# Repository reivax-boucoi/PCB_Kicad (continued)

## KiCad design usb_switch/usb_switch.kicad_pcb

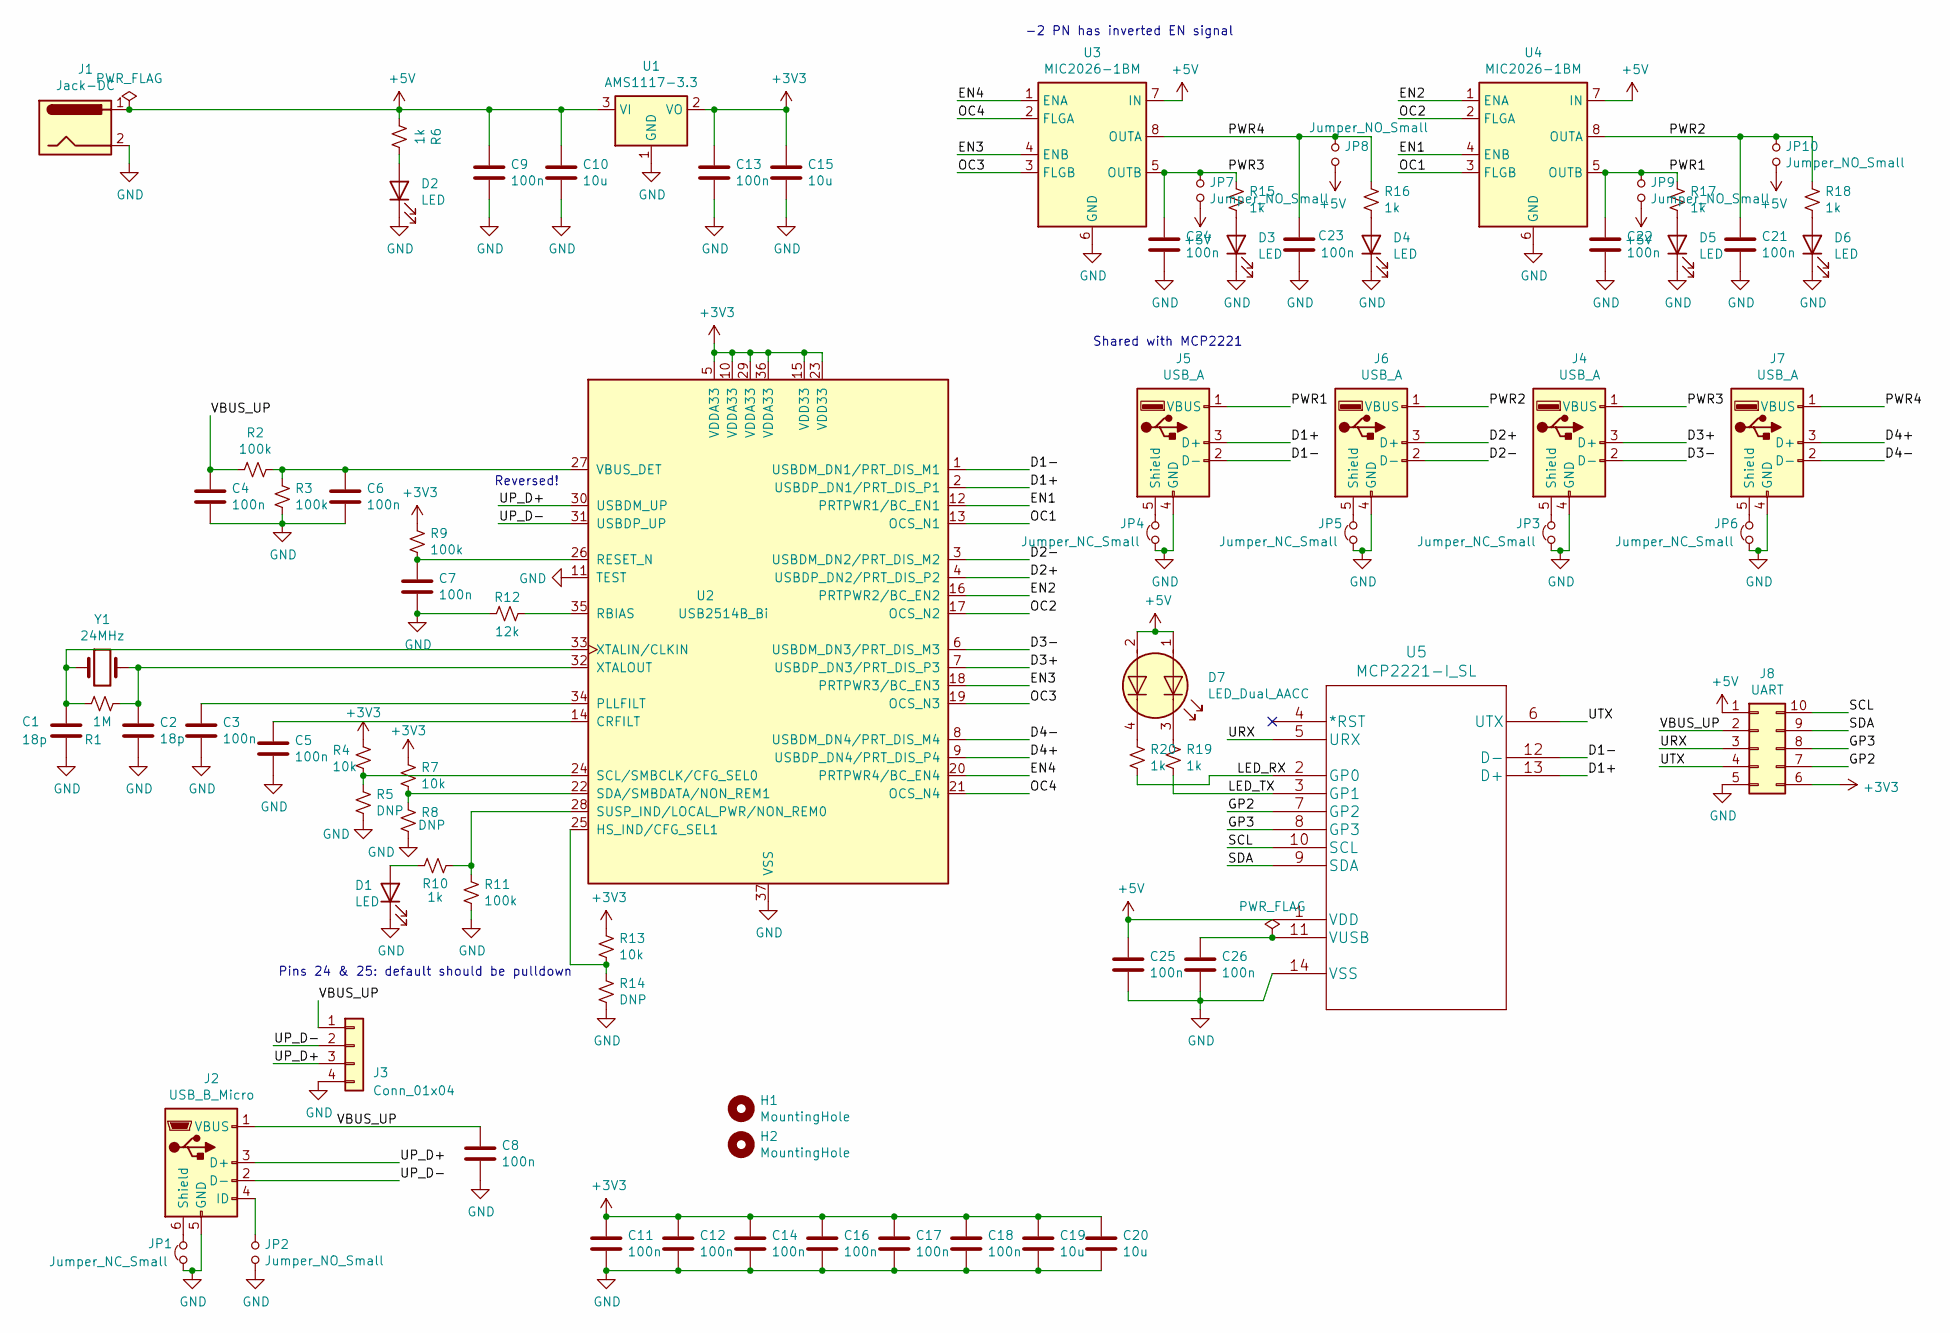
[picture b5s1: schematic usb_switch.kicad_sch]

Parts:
C1, C2: 18p; C_0603_1608Metric_Pad1.05x0.95mm_HandSolder
C3, C4, C5, C6, C7, C8, C9, C11, C12, C13, C14, C16, C17, C18, C21, C22, C23, C24, C25, C26: 100n; C_0603_1608Metric_Pad1.05x0.95mm_HandSolder
C10, C15, C19, C20: 10u; C_0603_1608Metric_Pad1.05x0.95mm_HandSolder
D1, D2, D3, D4, D5, D6: LED; LED_0603_1608Metric_Pad1.05x0.95mm_HandSolder
D7: LED_Dual_AACC; LED_SK6812_EC15_1.5x1.5mm
H1, H2: MountingHole; MountingHole_2.2mm_M2
J1: Jack-DC; BarrelJack_Wuerth_6941xx301002
J2: USB_B_Micro; USB_Micro-B_Molex_47346-0001
J3: Conn_01x04; PinSocket_1x04_P2.54mm_Vertical
J4, J5, J6, J7: USB_A; USB_A_Stewart_SS-52100-001_Horizontal
J8: UART; PinSocket_2x05_P2.54mm_Horizontal
JP1, JP3, JP4, JP5, JP6: Jumper_NC_Small; SolderJumper-2_P1.3mm_Bridged_RoundedPad1.0x1.5mm
JP2, JP7, JP8, JP9, JP10: Jumper_NO_Small; SolderJumper-2_P1.3mm_Open_RoundedPad1.0x1.5mm
R1: 1M; R_0603_1608Metric_Pad1.05x0.95mm_HandSolder
R2, R3, R9, R11: 100k; R_0603_1608Metric_Pad1.05x0.95mm_HandSolder
R4, R7, R13: 10k; R_0603_1608Metric_Pad1.05x0.95mm_HandSolder
R5, R8, R14: DNP; R_0603_1608Metric_Pad1.05x0.95mm_HandSolder
R6, R10, R15, R16, R17, R18, R20: 1k; R_0603_1608Metric_Pad1.05x0.95mm_HandSolder
R12: 12k; R_0603_1608Metric_Pad1.05x0.95mm_HandSolder
R19: 1k; R_0603_1608Metric
U1: AMS1117-3.3; SOT-223-3_TabPin2
U2: USB2514B_Bi; QFN-36-1EP_6x6mm_P0.5mm_EP3.7x3.7mm
U3, U4: MIC2026-1BM; SOIC-8_3.9x4.9mm_P1.27mm
U5: MCP2221-I_SL
Y1: 24MHz; Crystal_SMD_HC49-SD

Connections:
+3V3: C11.1, C12.1, C13.1, C14.1, C15.1, C16.1, C17.1, C18.1, C19.1, C20.1, J8.6, R4.1, R7.1, R9.1, R13.1, U1.2 (VO), U2.5 (VDDA33), U2.10 (VDDA33), U2.15 (VDD33), U2.23 (VDD33), U2.29 (VDDA33), U2.36 (VDDA33)
+5V: C9.1, C10.1, C25.1, D7.1 (A1), D7.2 (A2), J1.1, J8.1, JP7.2, JP8.2, JP9.2, JP10.2, R6.1, U1.3 (VI), U3.7 (IN), U4.7 (IN), U5.1 (VDD)
/D1+: J5.3 (D+), U2.2 (USBDP_DN1/PRT_DIS_P1), U5.13 (D+)
/D1-: J5.2 (D-), U2.1 (USBDM_DN1/PRT_DIS_M1), U5.12 (D-)
/D2+: J6.3 (D+), U2.4 (USBDP_DN2/PRT_DIS_P2)
/D2-: J6.2 (D-), U2.3 (USBDM_DN2/PRT_DIS_M2)
/D3+: J4.3 (D+), U2.7 (USBDP_DN3/PRT_DIS_P3)
/D3-: J4.2 (D-), U2.6 (USBDM_DN3/PRT_DIS_M3)
/D4+: J7.3 (D+), U2.9 (USBDP_DN4/PRT_DIS_P4)
/D4-: J7.2 (D-), U2.8 (USBDM_DN4/PRT_DIS_M4)
/EN1: U2.12 (PRTPWR1/BC_EN1), U4.4 (ENB)
/EN2: U2.16 (PRTPWR2/BC_EN2), U4.1 (ENA)
/EN3: U2.18 (PRTPWR3/BC_EN3), U3.4 (ENB)
/EN4: U2.20 (PRTPWR4/BC_EN4), U3.1 (ENA)
/GP2: J8.7, U5.7 (GP2)
/GP3: J8.8, U5.8 (GP3)
/LED_RX: R20.2, U5.2 (GP0)
/LED_TX: R19.2, U5.3 (GP1)
/OC1: U2.13 (OCS_N1), U4.3 (FLGB)
/OC2: U2.17 (OCS_N2), U4.2 (FLGA)
/OC3: U2.19 (OCS_N3), U3.3 (FLGB)
/OC4: U2.21 (OCS_N4), U3.2 (FLGA)
/PWR1: C22.1, J5.1 (VBUS), JP9.1, R17.1, U4.5 (OUTB)
/PWR2: C21.1, J6.1 (VBUS), JP10.1, R18.1, U4.8 (OUTA)
/PWR3: C24.1, J4.1 (VBUS), JP7.1, R15.1, U3.5 (OUTB)
/PWR4: C23.1, J7.1 (VBUS), JP8.1, R16.1, U3.8 (OUTA)
/SCL: J8.10, U5.10 (SCL)
/SDA: J8.9, U5.9 (SDA)
/UP_D+: J2.3 (D+), J3.3, U2.30 (USBDM_UP)
/UP_D-: J2.2 (D-), J3.2, U2.31 (USBDP_UP)
/URX: J8.3, U5.5 (URX)
/UTX: J8.4, U5.6 (UTX)
/VBUS_UP: C4.1, C8.1, J2.1 (VBUS), J3.1, J8.2, R2.2
GND: C1.2, C2.2, C3.2, C4.2, C5.2, C6.2, C7.2, C8.2, C9.2, C10.2, C11.2, C12.2, C13.2, C14.2, C15.2, C16.2, C17.2, C18.2, C19.2, C20.2, C21.2, C22.2, C23.2, C24.2, C25.2, C26.2, D1.1 (K), D2.1 (K), D3.1 (K), D4.1 (K), D5.1 (K), D6.1 (K), J1.2, J2.5 (GND), J3.4, J4.4 (GND), J5.4 (GND), J6.4 (GND), J7.4 (GND), J8.5, JP1.1, JP2.2, JP3.1, JP4.1, JP5.1, JP6.1, R3.2, R5.2, R8.2, R11.2, R12.2, R14.2, U1.1 (GND), U2.11 (TEST), U2.37 (VSS), U3.6 (GND), U4.6 (GND), U5.14 (VSS)
unnamed: C1.1, R1.1, U2.33 (XTALIN/CLKIN), Y1.1
unnamed: C2.1, R1.2, U2.32 (XTALOUT), Y1.2
unnamed: C3.1, U2.34 (PLLFILT)
unnamed: C5.1, U2.14 (CRFILT)
unnamed: C6.1, R2.1, R3.1, U2.27 (VBUS_DET)
unnamed: C7.1, R9.2, U2.26 (RESET_N)
unnamed: C26.1, U5.11 (VUSB)
unnamed: D1.2 (A), R10.1
unnamed: D2.2 (A), R6.2
unnamed: D3.2 (A), R15.2
unnamed: D4.2 (A), R16.2
unnamed: D5.2 (A), R17.2
unnamed: D6.2 (A), R18.2
unnamed: D7.3 (K1), R19.1
unnamed: D7.4 (K2), R20.1
unnamed: J2.4 (ID), JP2.1
unnamed: J2.6 (Shield), JP1.2
unnamed: J4.5 (Shield), JP3.2
unnamed: J5.5 (Shield), JP4.2
unnamed: J6.5 (Shield), JP5.2
unnamed: J7.5 (Shield), JP6.2
unnamed: R4.2, R5.1, U2.24 (SCL/SMBCLK/CFG_SEL0)
unnamed: R7.2, R8.1, U2.22 (SDA/SMBDATA/NON_REM1)
unnamed: R10.2, R11.1, U2.28 (SUSP_IND/LOCAL_PWR/NON_REM0)
unnamed: R12.1, U2.35 (RBIAS)
unnamed: R13.2, R14.1, U2.25 (HS_IND/CFG_SEL1)

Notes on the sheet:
Shared with MCP2221
Reversed!
Pins 24 & 25: default should be pulldown
-2 PN has inverted EN signal

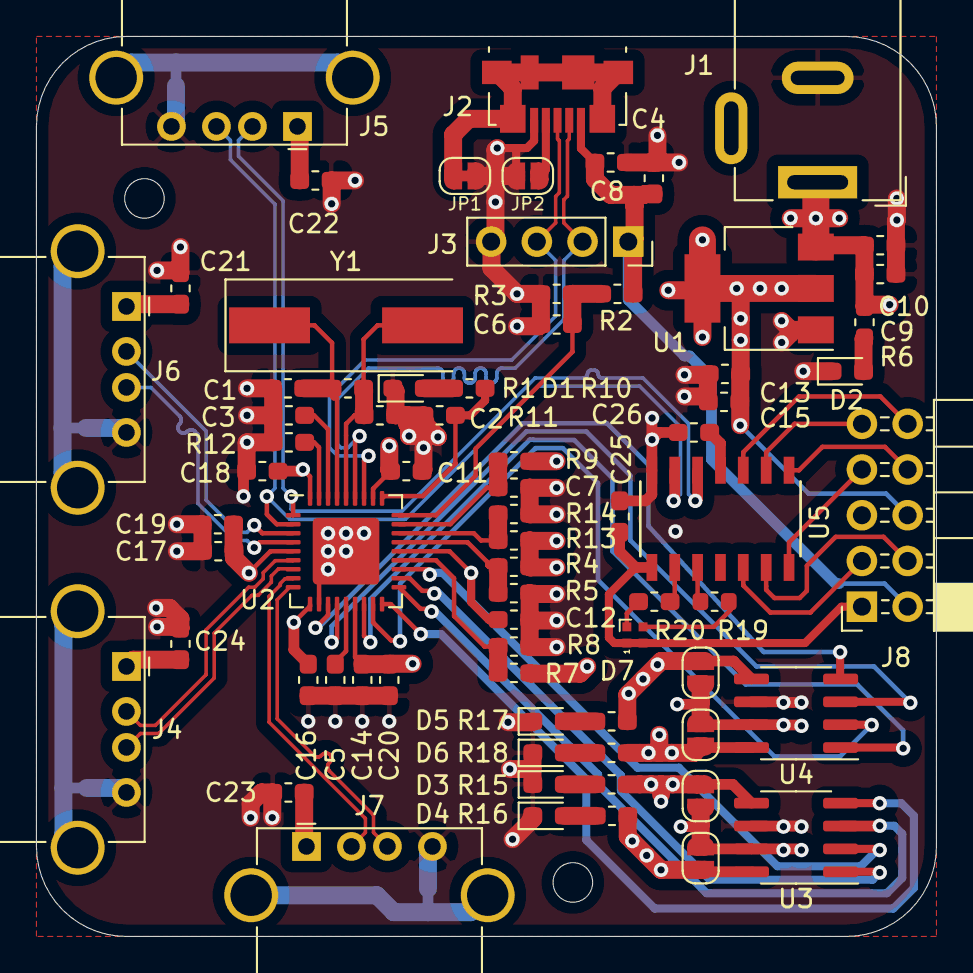
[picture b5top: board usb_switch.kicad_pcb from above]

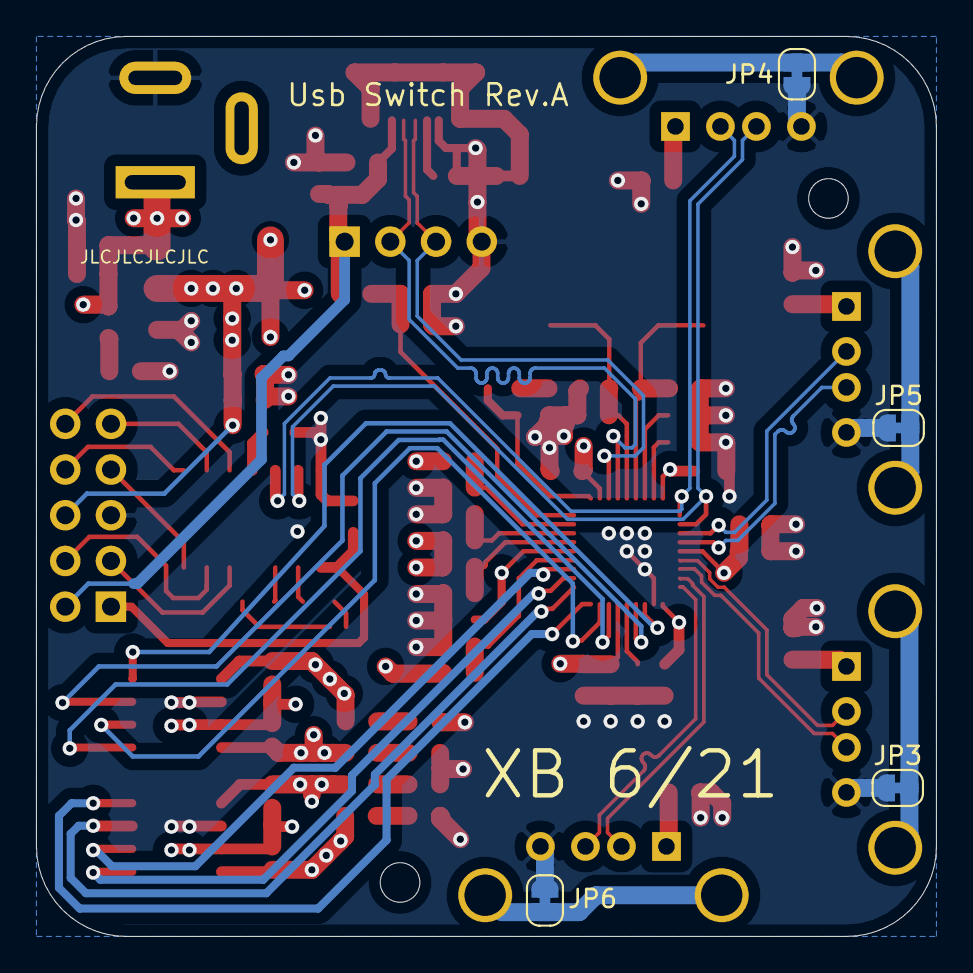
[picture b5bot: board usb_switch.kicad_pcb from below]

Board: 4 copper layers, 50.0 x 50.0 mm, 79 parts (4 on the bottom side), 60 nets.

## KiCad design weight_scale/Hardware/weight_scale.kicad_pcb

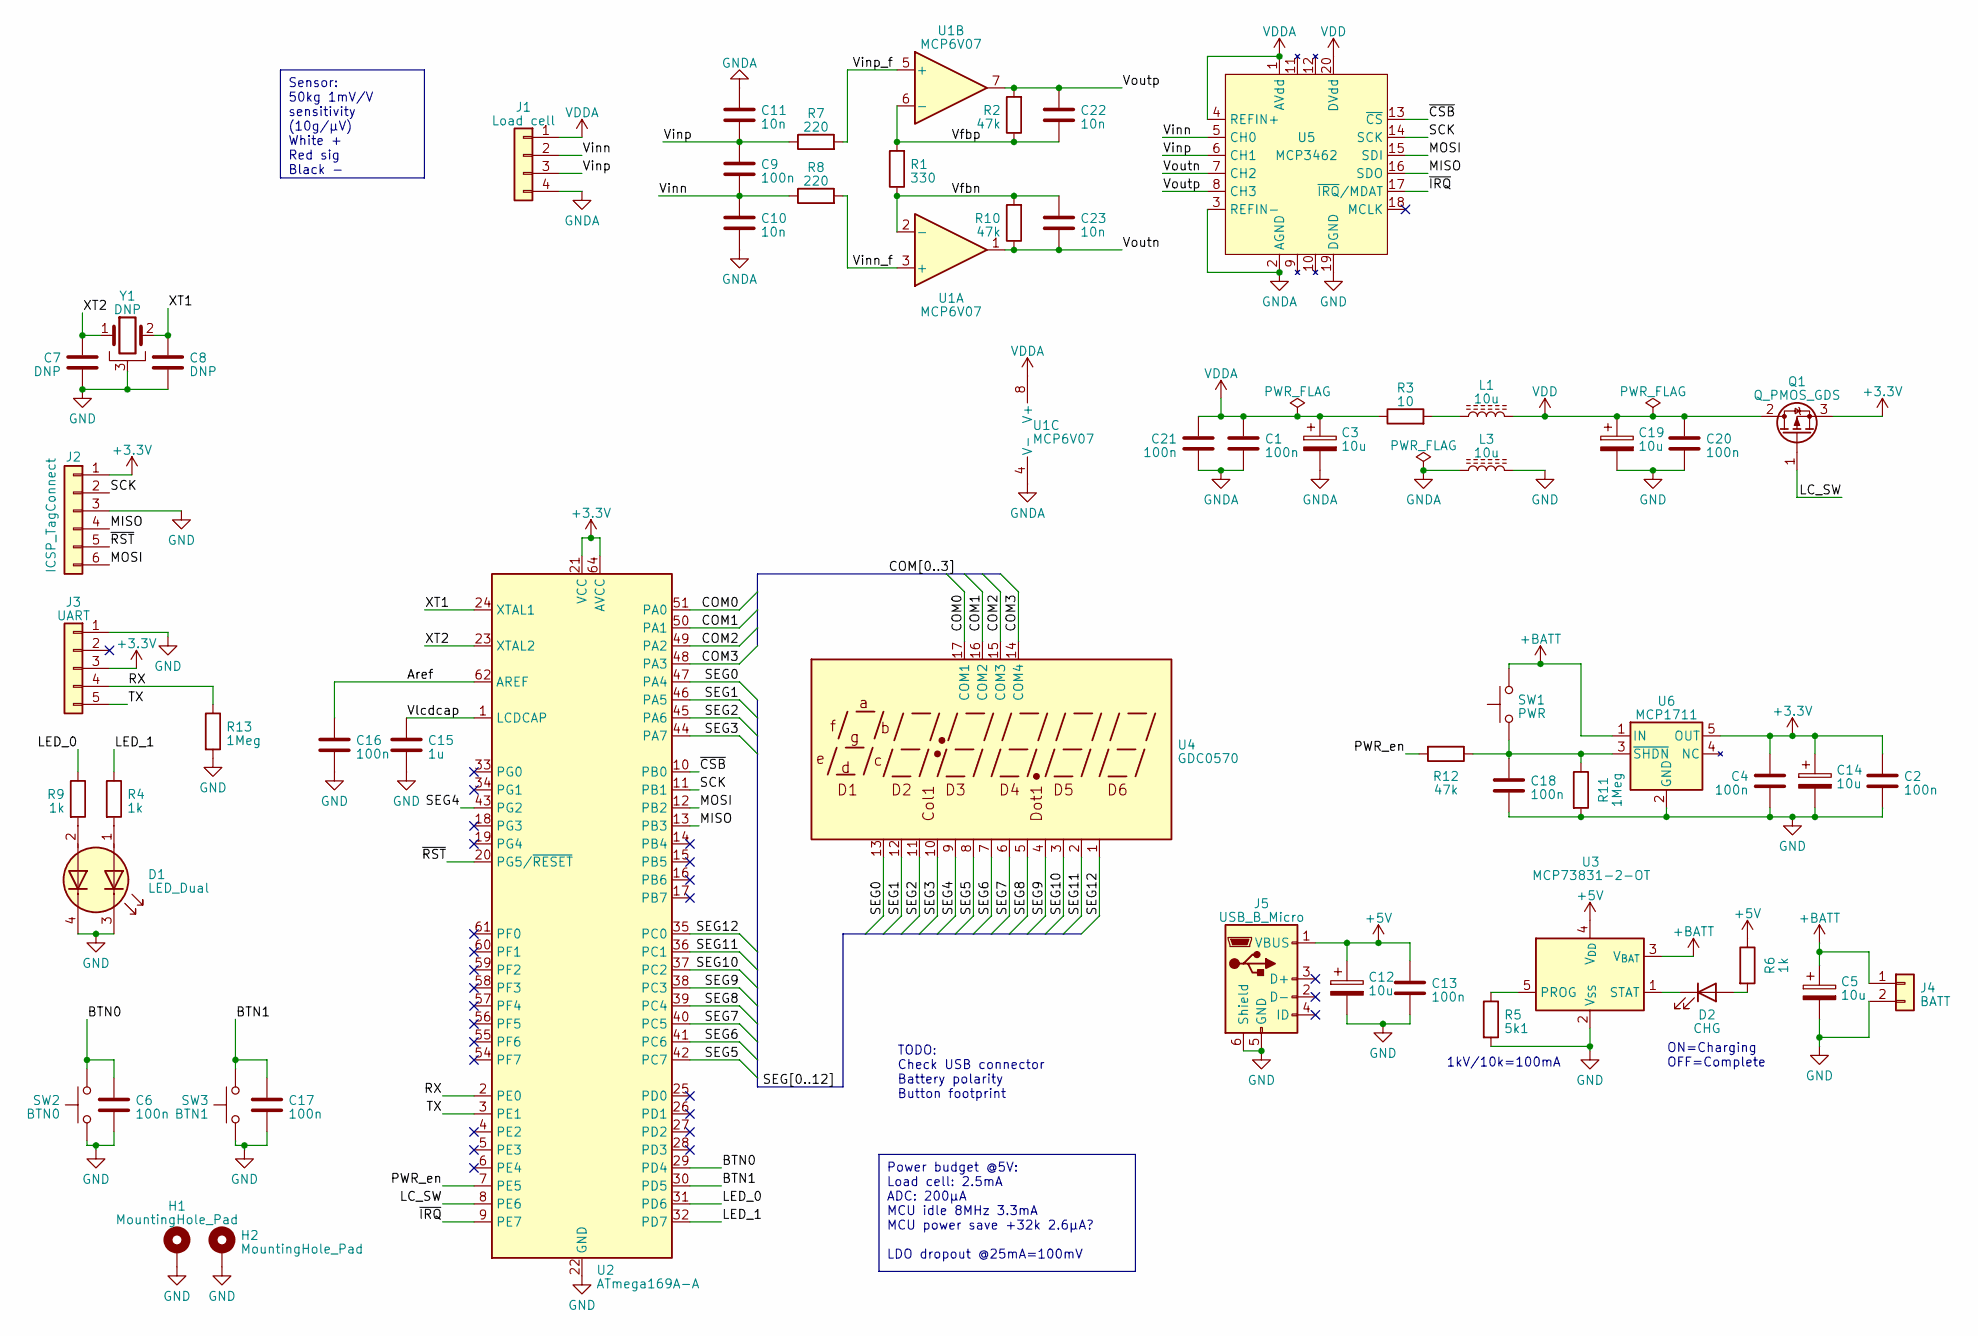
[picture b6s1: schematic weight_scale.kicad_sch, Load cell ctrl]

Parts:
C1, C2, C4, C6, C9, C13, C16, C17, C18, C20, C21: 100n; C_0805_2012Metric_Pad1.18x1.45mm_HandSolder
C3, C5, C12, C14, C19: 10u; C_1206_3216Metric_Pad1.33x1.80mm_HandSolder
C7, C8: DNP; C_0805_2012Metric_Pad1.18x1.45mm_HandSolder
C10, C11, C22, C23: 10n; C_0805_2012Metric_Pad1.18x1.45mm_HandSolder
C15: 1u; C_0805_2012Metric_Pad1.18x1.45mm_HandSolder
D1: LED_Dual; LED_Cree-PLCC4_3.2x2.8mm_CCW
D2: CHG; LED_0805_2012Metric_Pad1.15x1.40mm_HandSolder
H1, H2: MountingHole_Pad; MountingHole_3.2mm_M3_Pad_Via
J1: Load cell; 282834-4
J2: ICSP_TagConnect; Tag-Connect_TC2030-IDC-NL_2x03_P1.27mm_Vertical
J3: UART; PinSocket_1x05_P2.54mm_Vertical
J4: BATT; PinHeader_1x02_P2.54mm_Vertical
J5: USB_B_Micro; USB_Mini-B_Wuerth_65100516121_Horizontal
L1, L3: 10u; L_0805_2012Metric_Pad1.15x1.40mm_HandSolder
Q1: Q_PMOS_GDS; SOT-89-3_Handsoldering
R1: 330; R_0805_2012Metric_Pad1.20x1.40mm_HandSolder
R2, R10, R12: 47k; R_0805_2012Metric_Pad1.20x1.40mm_HandSolder
R3: 10; R_0805_2012Metric_Pad1.20x1.40mm_HandSolder
R4, R6, R9: 1k; R_0805_2012Metric_Pad1.20x1.40mm_HandSolder
R5: 5k1; R_0805_2012Metric_Pad1.20x1.40mm_HandSolder
R7, R8: 220; R_0805_2012Metric_Pad1.20x1.40mm_HandSolder
R11, R13: 1Meg; R_0805_2012Metric_Pad1.20x1.40mm_HandSolder
SW1: PWR; SW_PUSH_6mm_2pins
SW2: BTN0; SW_PUSH_6mm_2pins
SW3: BTN1; SW_PUSH_6mm_2pins
U1: MCP6V07; SOIC-8_3.9x4.9mm_P1.27mm
U2: ATmega169A-A; TQFP-64_14x14mm_P0.8mm
U3: MCP73831-2-OT; SOT-23-5
U4: GDC0570; GDC0570_LCD_6digits_2mmPitch
U5: MCP3462; TSSOP-20_4.4x6.5mm_P0.65mm
U6: MCP1711; SOT-23-5
Y1: DNP; Crystal_C26-LF_D2.1mm_L6.5mm_Horizontal_1EP_style2

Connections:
+3.3V: C2.1, C4.1, C14.1, J2.1, J3.3, Q1.3 (S), U2.21 (VCC), U2.52 (VCC), U2.64 (AVCC), U6.5 (OUT)
+5V: C12.1, C13.1, J5.1 (VBUS), R6.1, U3.4 (V_{DD})
+BATT: C5.1, J4.1, SW1.2, U3.3 (V_{BAT}), U6.1 (IN)
/Aref: C16.1, U2.62 (AREF)
/BTN0: C6.1, SW2.2, U2.29 (PD4)
/BTN1: C17.1, SW3.2, U2.30 (PD5)
/COM0: U2.51 (PA0), U4.17 (COM1)
/COM1: U2.50 (PA1), U4.16 (COM2)
/COM2: U2.49 (PA2), U4.15 (COM3)
/COM3: U2.48 (PA3), U4.14 (COM4)
/LC_SW: Q1.1 (G), U2.8 (PE6)
/LED_0: R9.1, U2.31 (PD6)
/LED_1: R4.1, U2.32 (PD7)
/MISO: J2.4, U2.13 (PB3), U5.16 (SDO)
/MOSI: J2.6, U2.12 (PB2), U5.15 (SDI)
/PWR_en: R12.2, U2.7 (PE5)
/RX: J3.4, R13.1, U2.2 (PE0)
/SCK: J2.2, U2.11 (PB1), U5.14 (SCK)
/SEG0: U2.47 (PA4), U4.13
/SEG1: U2.46 (PA5), U4.12
/SEG2: U2.45 (PA6), U4.11
/SEG3: U2.44 (PA7), U4.10
/SEG4: U2.43 (PG2), U4.9
/SEG5: U2.42 (PC7), U4.8
/SEG6: U2.41 (PC6), U4.7
/SEG7: U2.40 (PC5), U4.6
/SEG8: U2.39 (PC4), U4.5
/SEG9: U2.38 (PC3), U4.4
/SEG10: U2.37 (PC2), U4.3
/SEG11: U2.36 (PC1), U4.2
/SEG12: U2.35 (PC0), U4.1
/TX: J3.5, U2.3 (PE1)
/Vfbn: C23.1, R1.1, R10.2, U1.2 (-)
/Vfbp: C22.2, R1.2, R2.1, U1.6 (-)
/Vinn: C9.2, C10.1, J1.2, R8.1, U5.5 (CH0)
/Vinn_f: R8.2, U1.3 (+)
/Vinp: C9.1, C11.2, J1.3, R7.1, U5.6 (CH1)
/Vinp_f: R7.2, U1.5 (+)
/Vlcdcap: C15.1, U2.1 (LCDCAP)
/Voutn: C23.2, R10.1, U1.1, U5.7 (CH2)
/Voutp: C22.1, R2.2, U1.7, U5.8 (CH3)
/XT1: C8.1, U2.24 (XTAL1), Y1.2
/XT2: C7.1, U2.23 (XTAL2), Y1.1
/~CSB: U2.10 (PB0), U5.13 (~CS)
/~IRQ: U2.9 (PE7), U5.17 (~IRQ/MDAT)
/~RST: J2.5, U2.20 (PG5/~RESET)
GND: C2.2, C4.2, C5.2, C6.2, C7.2, C8.2, C12.2, C13.2, C14.2, C15.2, C16.2, C17.2, C18.2, C19.2, C20.2, D1.3 (K1), D1.4 (K2), H1.1, H2.1, J2.3, J3.1, J4.2, J5.5 (GND), J5.6 (Shield), L3.2, R5.2, R11.2, R13.2, SW2.1, SW3.1, U2.22 (GND), U2.53 (GND), U2.63 (GND), U3.2 (V_{SS}), U5.19 (DGND), U6.2 (GND), Y1.3
GNDA: C1.2, C3.2, C10.2, C11.1, C21.2, J1.4, L3.1, U1.4 (V-), U5.2 (AGND), U5.3 (REFIN-)
unnamed: D1.1 (A1), R4.2
unnamed: D1.2 (A2), R9.2
unnamed: D2.2 (A), R6.2
unnamed: D2.1 (K), U3.1 (STAT)
unnamed: L1.1, R3.2
unnamed: R5.1, U3.5 (PROG)
unnamed: C18.1, R11.1, R12.1, SW1.1, U6.3 (~SHDN)
VDD: C19.1, C20.1, L1.2, Q1.2 (D), U5.20 (DVdd)
VDDA: C1.1, C3.1, C21.1, J1.1, R3.1, U1.8 (V+), U5.1 (AVdd), U5.4 (REFIN+)

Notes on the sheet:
Sensor: 50kg 1mV/V sensitivity (10g/µV) White + Red sig Black -
Power budget @5V: Load cell: 2.5mA ADC: 200µA MCU idle 8MHz 3.3mA MCU power save +32k 2.6µA? LDO dropout @25mA=100mV
1kV/10k=100mA
TODO: Check USB connector Battery polarity Button footprint
ON=Charging OFF=Complete

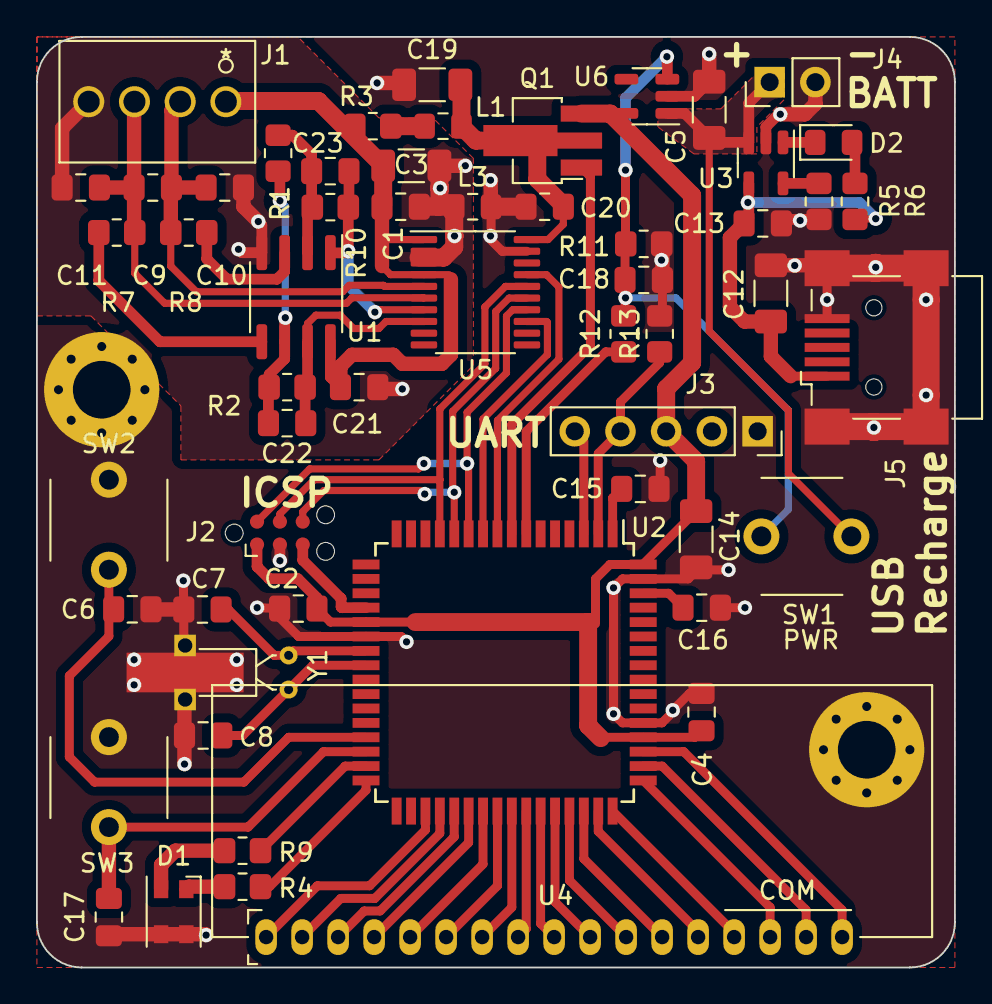
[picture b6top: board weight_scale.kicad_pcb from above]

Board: 2 copper layers, 51.0 x 51.7 mm, 58 parts (0 on the bottom side), 57 nets.
